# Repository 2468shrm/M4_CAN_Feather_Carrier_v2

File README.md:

# M4_CAN_Feather_Carrier_v2

## Board Layout

## Disclaimer
While I've tested a prior version of this board, this board is to be considered
alpha and subject to bugs and errors. Use at your own risk. However the Gerbers
are provided should you want to fabricate your own.

## Introduction
The carrier board is an adaptor to make using the Adafruit M4 CAN Express
Feather board more useful in FRC applications. This board was designed by mentors
of FRC2468/2687/2689. An initial version was done early in 2022, fabricated at JLCPCB
and tested to a limited degree. During the testing some weaknesses were identified and
initial design decisions questioned. Hence V2. Neither has received any actual FRC
use (it was not used by any of our teams during the 2022 competition season). However
a small number of these boards will be fabricated after the kickoff to the 2023 season.

This is the board as referenced in the [frc_can](https://github.com/2468shrm/frc_can)
project's CANCarrierBoard module (in
[can_carrier_board.py](https://github.com/2468shrm/frc_can/blob/main/can_carrier_board.py)).

## Board Description
The carrier board provides the following:
- Power interface (J1)
  - Power comes from a 12V supply through the provided 2-input screw terminal
  - The power supply contains a diode capacitor circuit to reduce the effects of FRC robot brownouts
- CAN interface
  - On the feather board
  - Note the feather board comes with termination included and active, so you must cut the termination trace jumper
- Analog I/O (AIO)
  - 4 analog inputs
  - Buffered with a unity gain opamp
  - Proded by 3-pin interface (similar to AIO on RoboRIO)
    - Pin 1: input analog signal
    - Pin 2: 3.3V supply
    - Pin 3: Ground
  - 3.3V input, max
- Digital I/O (DIO)
  - 4 digital inputs
  - Buffered with a level shifter
  - Selectable sensor voltage (VDD): 3.3V or 5V (all inputs share)
    - VDD selected by a jumper (J5)
    - 1-2 selects 3.3V
    - 2-3 selects 5V
  - Proded by 3-pin interface (similar to AIO on RoboRIO)
    - Pin 1: input analog signal
    - Pin 2: VDD supply
    - Pin 3: Ground
- Additional sensor power (J4)
	- A 2x4 header provided to provide additional VDD power to sensors
    - Intended for Adafruit beam break emitters or other multi-part sensors using an emitter and receiver pair where the receiver connects to DIO and emitter connects to the additional sensor power
- STEMMA QT/QWIIC (X1, X2, X3, X4)
  - 4 interfaces provided
- Neopixel (J2)
  - A Neopixel interface provided via a 3-input screw terminal
  - Intended to allow sensor to provide state of the sensor both over CAN and visually (i.e. sensor could be disconnected while still being useful)

## Power Interface
The initial version of this board was designed at the height of the pandemic's supply
chain shortage and so while I wanted to provide a 3A 5V supply (from 12V source) finding
the components was problematic at best. So I found a cheap, simple power supply module I
could acquire on Amazon. So I used it.

## DIO Level Shifter
The DIO interface has a level shifter between pins and MCU. The level shifter
A-side is 3.3V signaling due to the feather board's MCU requirements. The A-side
is expected to use internal pull ups if necessary. The B-side is VDD signaling
and is selected by the J5 jumper. The B-side pull ups are powered from the VDD
supply too.

The level shifter IC enable is driven by an MCU digital I/O and defaults to
off through a pull down resistor. Software must drive the OE signal high.

## Analog Buffer
A quad rail-to-rail opamp is used in unity-gain/follower configuration to buffer the
input signals to the MCU's ADCs. This is done so that sensors with large output
impedance may be connected to the ADC without significant loss in accuracy. Having
designed MCUs in the past, I'm quite aware of the effects on accuracy when using
potentiometers of 5K ohm. Most ADCs in MCUs have internal resistance and capacitacnce
that requires a low (80 ohm) source impedance to maintain spec'd accuracy.

## Updating the Programming
A switch (SW1, beside the power module) is provided to isolate the 5V generated by the
Weewooday module (U1) and the boost regulator on the Feather board. When programming a USB-C
cable is connected and the 5V is supplied on the feather board from this path. This would
lead to a contended supply. So, before programming change SW1 to open and plug in the board
to a host. Disconnect and change SW1 to closed to return to robot-supplied power.

# 3D Views of the Board
## Top

## Iso Front

## Iso Back

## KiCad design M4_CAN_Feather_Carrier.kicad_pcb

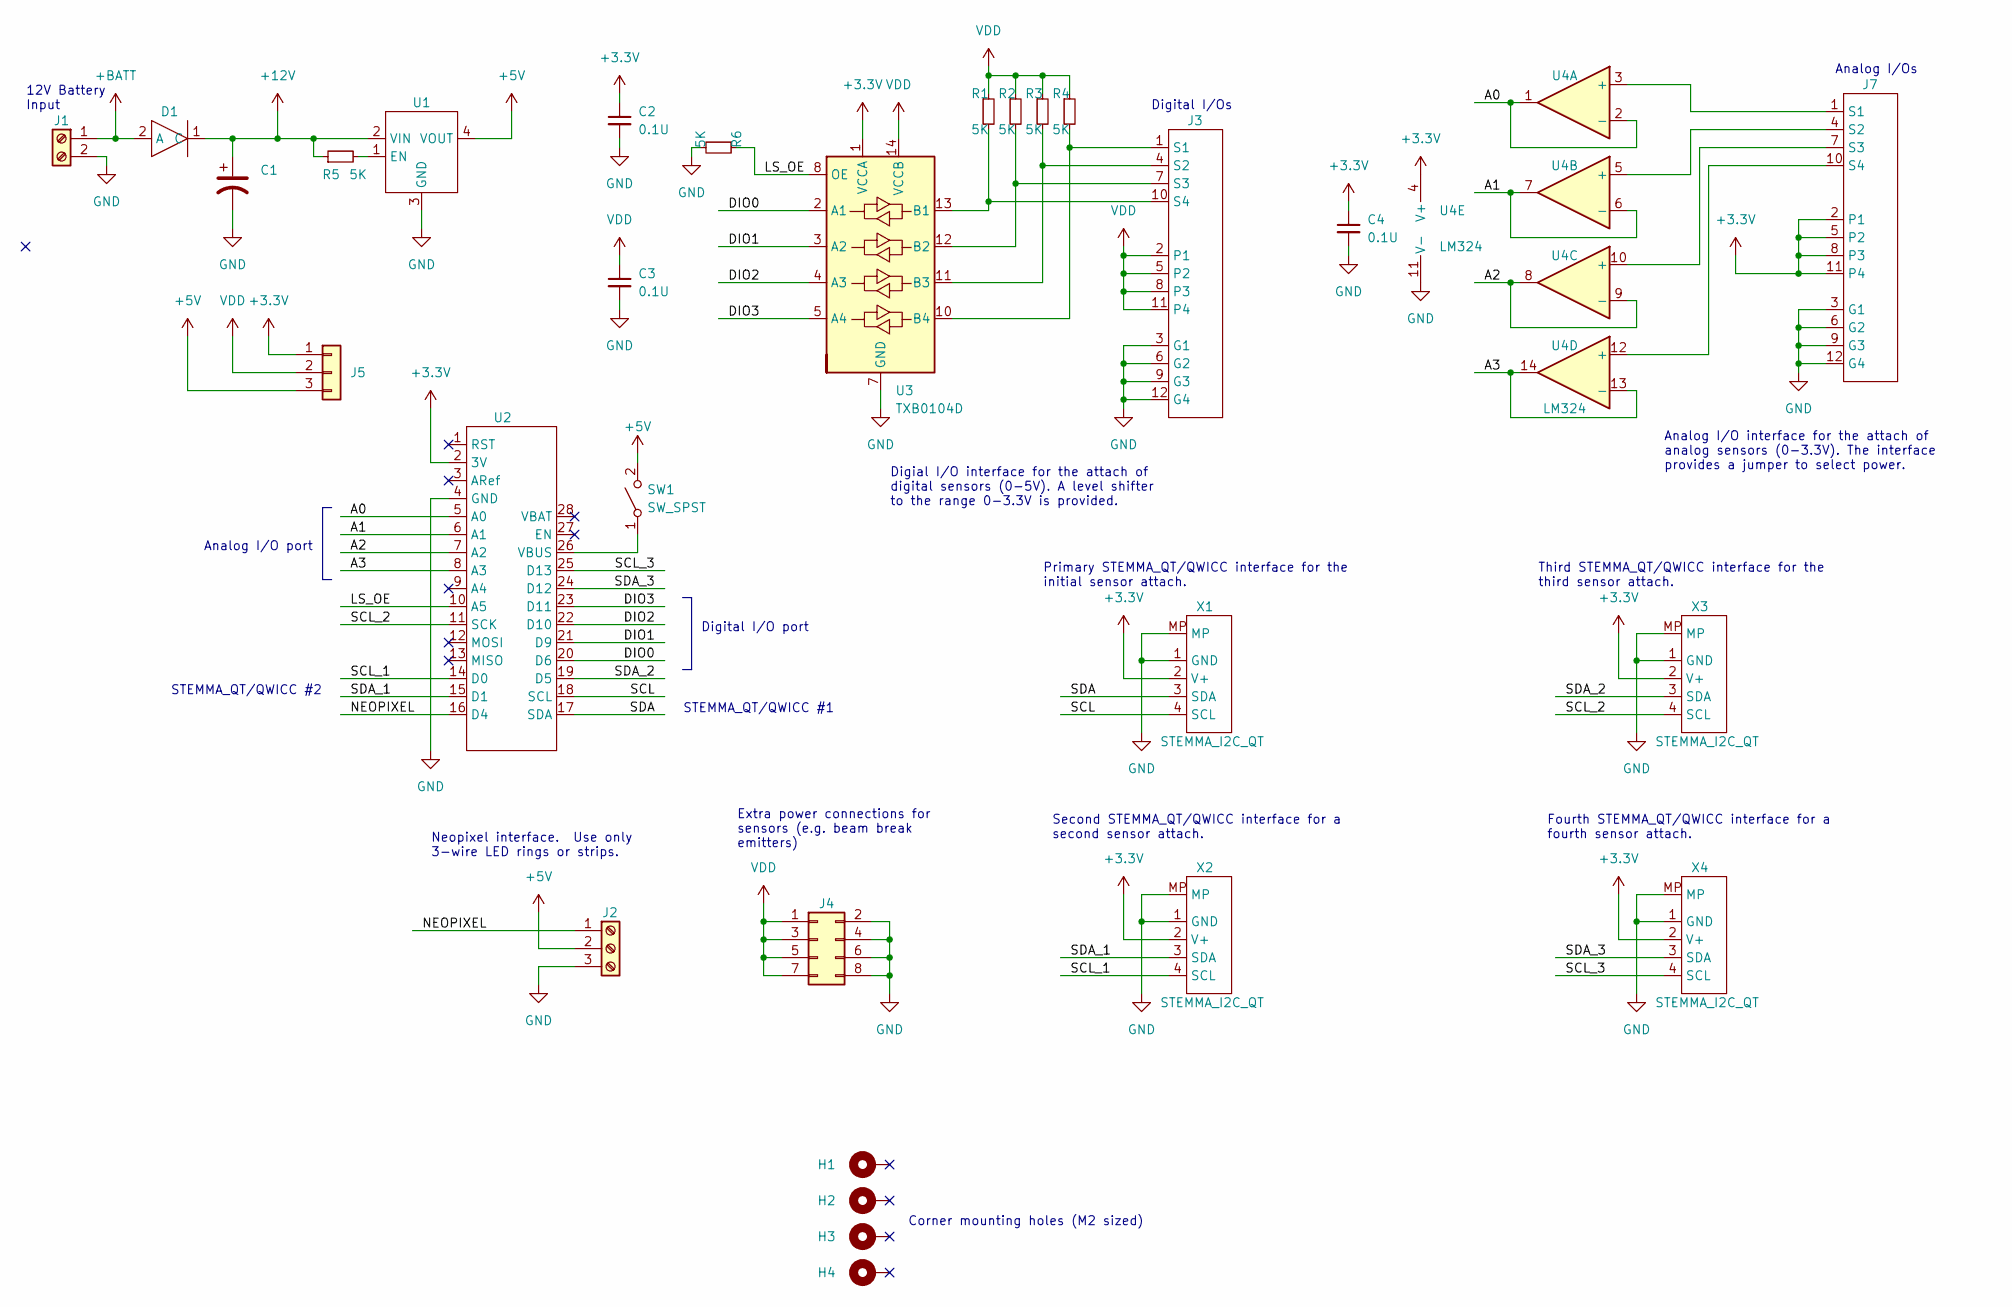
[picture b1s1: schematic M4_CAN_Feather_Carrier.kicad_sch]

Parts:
C1: 10u; CP_Elec_8x10
C2, C3, C4: 0.1U; C_0805_2012Metric
D1: UPR20e3; DO-216
H1, H2, H3, H4: MountingHole_Pad; MountingHole_2.2mm_M2_DIN965_Pad
J1: Screw_Terminal_01x02; TerminalBlock_4Ucon_1x02_P3.50mm_Horizontal
J2: Screw_Terminal_01x03; TerminalBlock_4Ucon_1x03_P3.50mm_Horizontal
J3, J7: conn_04_03; conn_04x03
J4: Conn_02x04_Odd_Even; PinHeader_2x04_P2.54mm_Vertical
J5: Conn_01x03; PinHeader_1x03_P2.54mm_Vertical
R1, R2, R3, R4, R5, R6: 5K; R_0805_2012Metric
SW1: SW_SPST; SPST-KJ01
U1: Weewooday-820
U2: Feather_M4_CAN_Express
U3: TXB0104D; SOIC-14_3.9x8.7mm_P1.27mm
U4: LM324; SOIC-14_3.9x8.7mm_P1.27mm
X1, X2, X3, X4: STEMMA_I2C_QT; JST_SH_SM04B-SRSS-TB_1x04-1MP_P1.00mm_Horizontal

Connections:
+3.3V: C2.1, C4.1, J5.1, J7.2 (P1), J7.5 (P2), J7.8 (P3), J7.11 (P4), U2.2 (3V), U3.1 (VCCA), U4.4 (V+), X1.2 (V+), X2.2 (V+), X3.2 (V+), X4.2 (V+)
+5V: J2.2, J5.3, SW1.2 (B), U1.4 (VOUT)
+12V: C1.1, D1.1 (C), R5.1, U1.2 (VIN)
+BATT: D1.2 (A), J1.1
/A0: U2.5 (A0), U4.1, U4.2 (-)
/A1: U2.6 (A1), U4.6 (-), U4.7
/A2: U2.7 (A2), U4.8, U4.9 (-)
/A3: U2.8 (A3), U4.13 (-), U4.14
/DIO0: U2.20 (D6), U3.2 (A1)
/DIO1: U2.21 (D9), U3.3 (A2)
/DIO2: U2.22 (D10), U3.4 (A3)
/DIO3: U2.23 (D11), U3.5 (A4)
/LS_OE: R6.1, U2.10 (A5), U3.8 (OE)
/NEOPIXEL: J2.1, U2.16 (D4)
/SCL: U2.18 (SCL), X1.4 (SCL)
/SCL_1: U2.14 (D0), X2.4 (SCL)
/SCL_2: U2.11 (SCK), X3.4 (SCL)
/SCL_3: U2.25 (D13), X4.4 (SCL)
/SDA: U2.17 (SDA), X1.3 (SDA)
/SDA_1: U2.15 (D1), X2.3 (SDA)
/SDA_2: U2.19 (D5), X3.3 (SDA)
/SDA_3: U2.24 (D12), X4.3 (SDA)
GND: C1.2, C2.2, C3.2, C4.2, J1.2, J2.3, J3.3 (G1), J3.6 (G2), J3.9 (G3), J3.12 (G4), J4.2, J4.4, J4.6, J4.8, J7.3 (G1), J7.6 (G2), J7.9 (G3), J7.12 (G4), R6.2, U1.3 (GND), U2.4 (GND), U3.7 (GND), U4.11 (V-), X1.1 (GND), X1.MP, X2.1 (GND), X2.MP, X3.1 (GND), X3.MP, X4.1 (GND), X4.MP
unnamed: J3.1 (S1), R4.2, U3.10 (B4)
unnamed: J3.4 (S2), R3.2, U3.11 (B3)
unnamed: J3.7 (S3), R2.2, U3.12 (B2)
unnamed: J3.10 (S4), R1.2, U3.13 (B1)
unnamed: J7.1 (S1), U4.3 (+)
unnamed: J7.4 (S2), U4.5 (+)
unnamed: J7.7 (S3), U4.10 (+)
unnamed: J7.10 (S4), U4.12 (+)
unnamed: R5.2, U1.1 (EN)
unnamed: SW1.1 (A), U2.26 (VBUS)
VDD: C3.1, J3.2 (P1), J3.5 (P2), J3.8 (P3), J3.11 (P4), J4.1, J4.3, J4.5, J4.7, J5.2, R1.1, R2.1, R3.1, R4.1, U3.14 (VCCB)

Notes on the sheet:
Corner mounting holes (M2 sized)
Digital I/Os
Analog I/Os
Third STEMMA_QT/QWICC interface for the third sensor attach.
Primary STEMMA_QT/QWICC interface for the initial sensor attach.
Extra power connections for sensors (e.g. beam break emitters)
Digial I/O interface for the attach of digital sensors (0-5V). A level shifter to the range 0-3.3V is provided.
Second STEMMA_QT/QWICC interface for a second sensor attach.
Digital I/O port
Analog I/O port
STEMMA_QT/QWICC #1
12V Battery Input
STEMMA_QT/QWICC #2
Analog I/O interface for the attach of analog sensors (0-3.3V). The interface provides a jumper to select power.
Neopixel interface. Use only 3-wire LED rings or strips.
Fourth STEMMA_QT/QWICC interface for a fourth sensor attach.

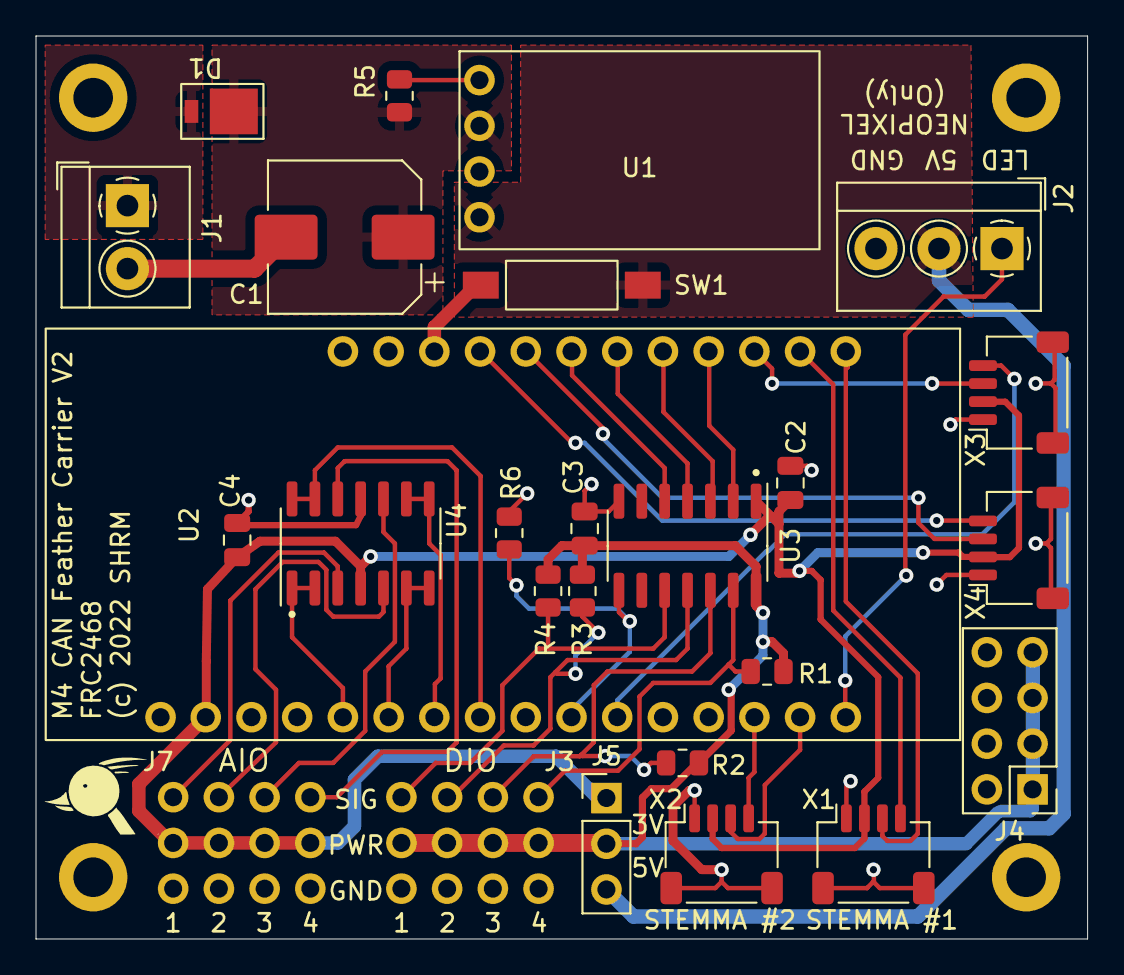
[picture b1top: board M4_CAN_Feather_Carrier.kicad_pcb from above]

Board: 2 copper layers, 58.4 x 50.2 mm, 30 parts (0 on the bottom side), 34 nets.

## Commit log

2022-12-26 board files, initial commit
2022-12-26 improved README
2022-12-26 more README improvements

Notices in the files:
M4_CAN_Feather_Carrier.kicad_pcb:
(c) 2022 SHRM
